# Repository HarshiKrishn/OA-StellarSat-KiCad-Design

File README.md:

# StellarSat ClimateSense - 1U CubeSat OBC

StellarSat ClimateSense is a 1U CubeSat mission focused on monitoring climate variations and atmospheric parameters from Low Earth Orbit (LEO).

## Mission Objective
To measure temperature, humidity, pressure, and air quality parameters and transmit data to a simulated ground station.

## System Architecture

### On-Board Computer (OBC)
- STM32 Microcontroller (Low-level control & sensor handling)
- Raspberry Pi Zero 2W (Data processing & formatting)

### Sensors
- BME280 – Temperature, Humidity & Pressure
- MQ-135 – Air Quality / CO₂ / NH₃
- DHT22 – Backup Temperature & Humidity

### Communication
- LoRa / RF simulation module
- Data formatted and transmitted to simulated ground station

## Simulation & Validation
- Proteus
- MATLAB
- OnShape

## 3D PCB View

### Top View

### Isometric View

### Bottom View

## 👤 Author

Designed and developed by Harshini  
Embedded Systems & PCB Design Enthusiast

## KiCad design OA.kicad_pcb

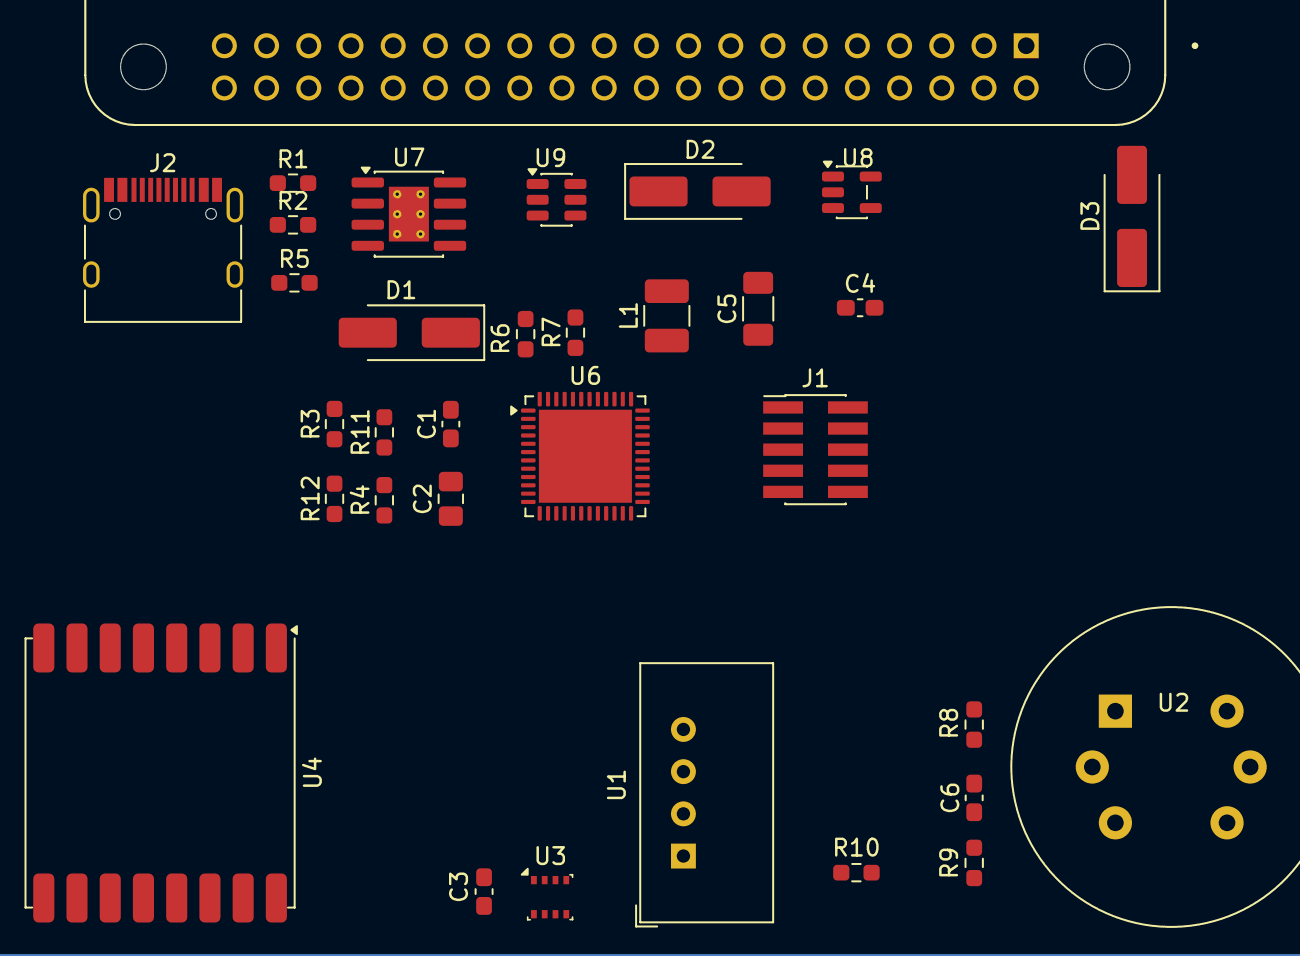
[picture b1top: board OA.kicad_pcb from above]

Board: 2 copper layers, 33 parts (0 on the bottom side), 39 nets, no tracks yet.

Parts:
C1: 0.1µF; C_0603_1608Metric_Pad1.08x0.95mm_HandSolder
C2: 4.7µF; C_0805_2012Metric_Pad1.18x1.45mm_HandSolder
C3, C4: 1µF; C_0603_1608Metric_Pad1.08x0.95mm_HandSolder
C5: 22µF; C_1206_3216Metric_Pad1.33x1.80mm_HandSolder
C6: 100nf; C_0603_1608Metric_Pad1.08x0.95mm_HandSolder
D1, D2, D3: SS14; D_SMA_Handsoldering
J1: Conn_ARM_JTAG_SWD_10; PinHeader_2x05_P1.27mm_Vertical_SMD
J2: USB_C_Receptacle_PowerOnly_24P; USB_C_Receptacle_HRO_TYPE-C-31-M-12
L1: 10µH; L_1210_3225Metric_Pad1.42x2.65mm_HandSolder
R1, R2: 5.1k; R_0603_1608Metric_Pad0.98x0.95mm_HandSolder
R3, R4, R10: 4.7k; R_0603_1608Metric_Pad0.98x0.95mm_HandSolder
R5: 2.4k; R_0603_1608Metric_Pad0.98x0.95mm_HandSolder
R6: 75k; R_0603_1608Metric_Pad0.98x0.95mm_HandSolder
R7, R8, R9: 10k; R_0603_1608Metric_Pad0.98x0.95mm_HandSolder
R11, R12: 22; R_0603_1608Metric_Pad0.98x0.95mm_HandSolder
U1: DHT22; ASAIR_AM2302_P2.54mm_Vertical
U2: MQ135; MQ-6
U3: BME280; Bosch_LGA-8_2.5x2.5mm_P0.65mm_ClockwisePinNumbering
U4: RFM95W-868S2; HOPERF_RFM9XW_SMD
U5: RASPBERRY_PI_ZERO_2_W; MODULE_RASPBERRY_PI_ZERO_2_W
U6: STM32F411CEUx; QFN-48-1EP_7x7mm_P0.5mm_EP5.6x5.6mm
U7: TP4056-42-ESOP8; SOIC-8-1EP_3.9x4.9mm_P1.27mm_EP2.41x3.3mm_ThermalVias
U8: LD3985G33R_TSOT23; TSOT-23-5
U9: MT3608; SOT-23-6

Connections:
3V3: C1.1, C1.2, C3.1, J1.1 (VTref), R8.2, R9.1, R10.1, U1.1 (VDD), U2.2 (A1), U2.5 (A2), U4.13 (3.3V), U6.1 (VBAT), U6.9 (VDDA), U6.24 (VDD), U6.36 (VDD), U6.48 (VDD), U8.5 (VOUT)
5_Vout: D2.2 (A), D3.2 (A), U2.1 (H1), U8.1 (VIN), U8.3 (INH)
+3.3V: R4.1, U3.2 (CSB)
GND: C2.2, C4.2, C5.2, C6.2, J1.3 (GND), J1.5 (GND), J1.9 (GNDDetect), J2.A1 (GND), J2.A12 (GND), J2.B1 (GND), J2.B12 (GND), J2.S1 (SHIELD), R1.1, R2.1, R3.2, R5.2, R6.2, R7.2, R9.2, U1.3 (GND), U1.4 (GND), U2.3 (B1), U2.4 (H2), U2.6 (B2), U3.1 (GND), U3.5 (SDO), U3.7 (GND), U4.1 (GND), U4.8 (GND), U4.10 (GND), U5.6 (GND_6), U5.9 (GND_9), U5.14 (GND_14), U5.20 (GND_20), U5.25 (GND_25), U5.30 (GND_30), U5.34 (GND_34), U5.39 (GND_39), U7.1 (TEMP), U7.3 (GND), U8.2 (GND), U9.2 (GND)
unnamed: D1.2 (A), U7.5 (BAT)
unnamed: D1.1 (K), U9.4 (EN), U9.5 (IN)
unnamed: C5.1, D2.1 (K), L1.2
unnamed: D3.1 (K), U5.2 (5V_2), U5.4 (5V_4)
unnamed: J1.4 (SWCLK/TCK), U6.3 (PC14)
unnamed: J1.2 (SWDIO/TMS), U6.2 (PC13)
unnamed: J1.6 (SWO/TDO), U6.39 (PB3)
unnamed: J1.10 (~RESET), R4.2, U6.7 (NRST)
unnamed: J2.A5 (CC1), R1.2
unnamed: J2.B5 (CC2), R2.2
unnamed: R10.2, U1.2 (SDA), U6.10 (PA0)
unnamed: U3.4 (SCK), U6.45 (PB8)
unnamed: U3.3 (SDI), U6.46 (PB9)
unnamed: C3.2, U3.6 (VDDIO), U3.8 (VDD)
unnamed: U4.14 (DIO0), U6.18 (PB0)
unnamed: U4.15 (DIO1), U6.26 (PB13)
unnamed: U4.2 (MISO), U6.16 (PA6)
unnamed: U4.3 (MOSI), U6.17 (PA7)
unnamed: U4.5 (NSS), U6.14 (PA4)
unnamed: U4.6 (RESET), U6.19 (PB1)
unnamed: U4.4 (SCK), U6.15 (PA5)
unnamed: U5.5 (GPIO3/SCL), U6.25 (PB12)
unnamed: R11.1, U5.8 (GPIO14/TXD0)
unnamed: R12.1, U5.10 (GPIO15/RXD0)
unnamed: R3.1, U6.44 (BOOT0)
unnamed: C6.1, R8.1, U6.11 (PA1)
unnamed: R12.2, U6.30 (PA9)
unnamed: R11.2, U6.31 (PA10)
unnamed: C2.1, U6.22 (VCAP1)
unnamed: U6.8 (VSSA), U6.23 (VSS), U6.35 (VSS), U6.47 (VSS), U6.49 (VSS)
unnamed: J2.A4 (VBUS), J2.A9 (VBUS), J2.B4 (VBUS), J2.B9 (VBUS), U7.4 (V_{CC}), U7.8 (CE)
unnamed: R5.1, U7.2 (PROG)
unnamed: C4.1, U8.4 (BYP)
unnamed: R6.1, R7.1, U9.3 (FB)
unnamed: L1.1, U9.1 (SW)

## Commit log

2026-02-19 Initial commit - CubeSat OBC KiCad design files
    Initial commit - CubeSat OBC KiCad design files
2026-02-19 Added 3D PCB renders
